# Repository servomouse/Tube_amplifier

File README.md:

Not that i am a fan of a high quality music, rather I love vacuum tubes and want to build something out of them. So, here it is: my vacuum tube headphone amplifier (but actually it can output up to 2 watts per channel). It is not finished yet, so the schematic may change during the experiments

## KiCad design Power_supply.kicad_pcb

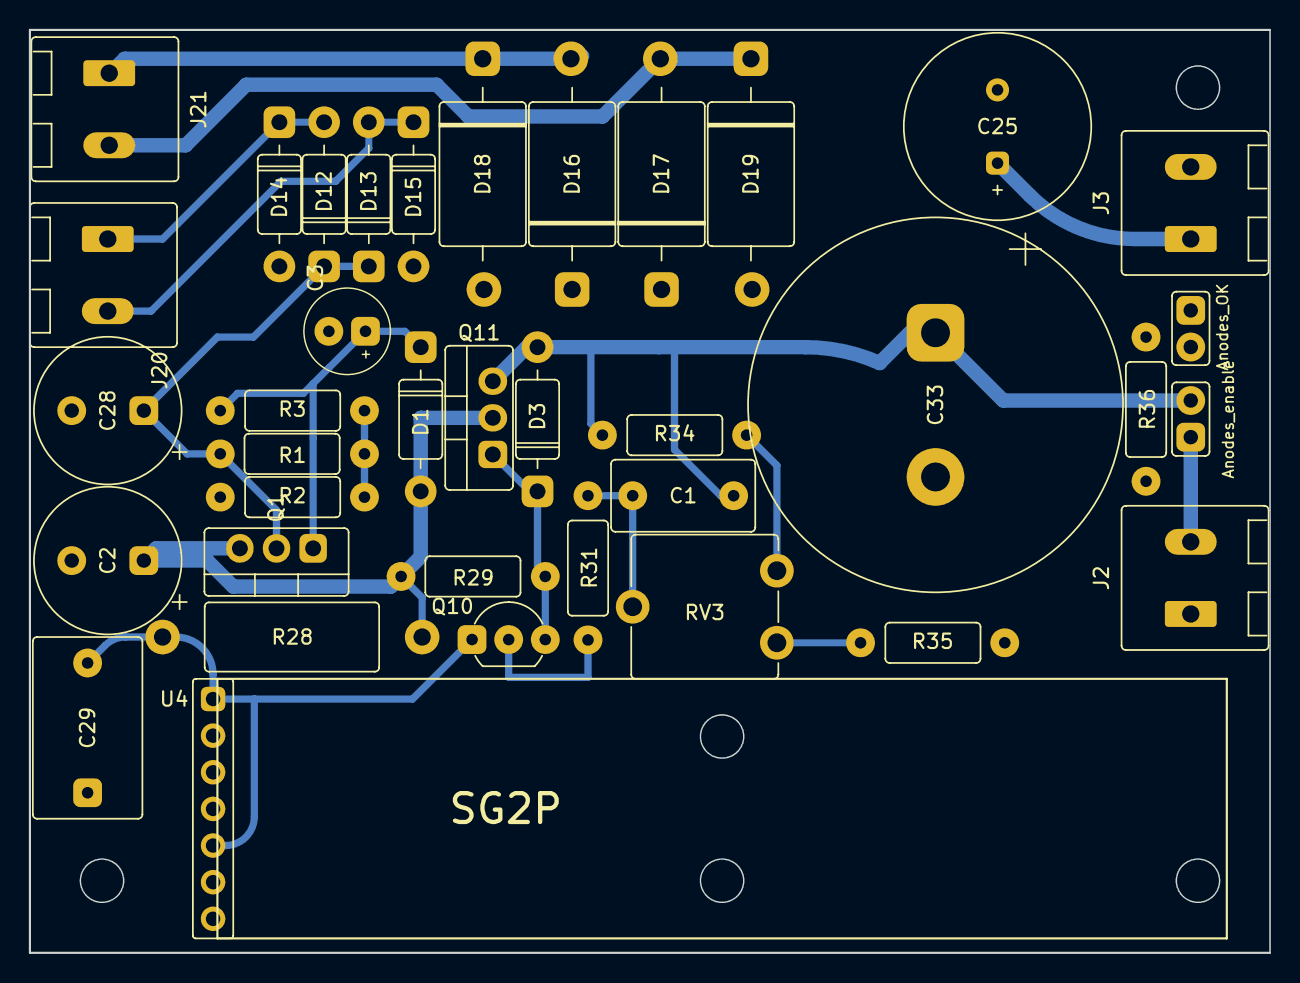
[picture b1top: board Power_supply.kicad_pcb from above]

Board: 2 copper layers, 86.0 x 64.0 mm, 37 parts (0 on the bottom side), 19 nets.

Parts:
C1: 33n; C_THT_K73-17_P7.00mm
C2, C28: 10uF; C_THT_D10.0mm_P5.00mm
C3: 2,2uF; C_THT_D5.0mm_P2.54mm
C25: 3300uF_10V; C_THT_D13mm_P5.08mm
C29: 100n; C_THT_K73-17_P9.00mm
C33: 100uF; CP_Radial_D22.0mm_P10.00mm_SnapIn
D1, D3: 1N4740A; D_DO-41_short
D12, D13, D14, D15: 1n4007; D_DO-41_short
D16, D17, D18, D19: 1N5821; D_DO-27_P16mm_Horizontal
J2: 240V; MCV_1,5_4-G-5.0_1x02_P5.0mm_Vertical
J3: 6V3; MCV_1,5_4-G-5.0_1x02_P5.0mm_Vertical
J20: HV_Transformer; MCV_1,5_4-G-5.0_1x02_P5.0mm_Vertical
J21: LV_Transformer; MCV_1,5_4-G-5.0_1x02_P5.0mm_Vertical
J25: Anodes_enable; PinHeader_1x02_P2.54mm
NE4: Anodes_OK; PinHeader_1x02_P2.54mm
Q1, Q11: STP4NK60ZFP(MJE13003); TO-220-3_Vertical
Q10: MPSA42; TO-92_Wide
R1: 330k; R_THT_025W
R2: 10M; R_THT_025W
R3: 100; R_THT_025W
R28: 13k; R_THT_1W
R29: 10k; R_THT_025W
R31: 100k; R_THT_025W
R34: 50k; R_THT_025W
R35: 40k; R_THT_025W
R36: 1M; R_THT_025W
RV3: 10k; Potentiometer_THT_CA9V
U4: SG2P; PinHeader_1x07_P2.54mm

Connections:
240V: J2.2, J25.1
+6V: C25.1, D16.1 (K), D17.1 (K), J3.1
GND: C2.2, C3.2, C25.2, C28.2, C29.1, C33.2, D14.2 (A), D15.2 (A), D18.2 (A), D19.2 (A), J2.1, J3.2, NE4.1, R2.1, R35.2, U4.2, U4.4, U4.7
HV: C28.1, D12.1 (K), D13.1 (K), Q1.2 (D), R1.2
unnamed: C1.1, R31.1, RV3.2
unnamed: C2.1, D1.2 (A), Q1.3 (S), Q11.2 (D), R28.1, R29.2
unnamed: C3.1, D1.1 (K), Q1.1 (G), R3.1
unnamed: C1.2, C33.1, D3.2 (A), J25.2, Q11.3 (S), R34.1, R36.2
unnamed: D3.1 (K), Q10.3 (C), Q11.1 (G), R29.1
unnamed: D12.2 (A), D14.1 (K), J20.1
unnamed: D13.2 (A), D15.1 (K), J20.2
unnamed: D16.2 (A), D18.1 (K), J21.1
unnamed: D17.2 (A), D19.1 (K), J21.2
unnamed: NE4.2, R36.1
unnamed: Q10.2 (B), R31.2
unnamed: C29.2, Q10.1 (E), R28.2, U4.1, U4.5
unnamed: R1.1, R2.2, R3.2
unnamed: R34.2, RV3.1
unnamed: R35.1, RV3.3

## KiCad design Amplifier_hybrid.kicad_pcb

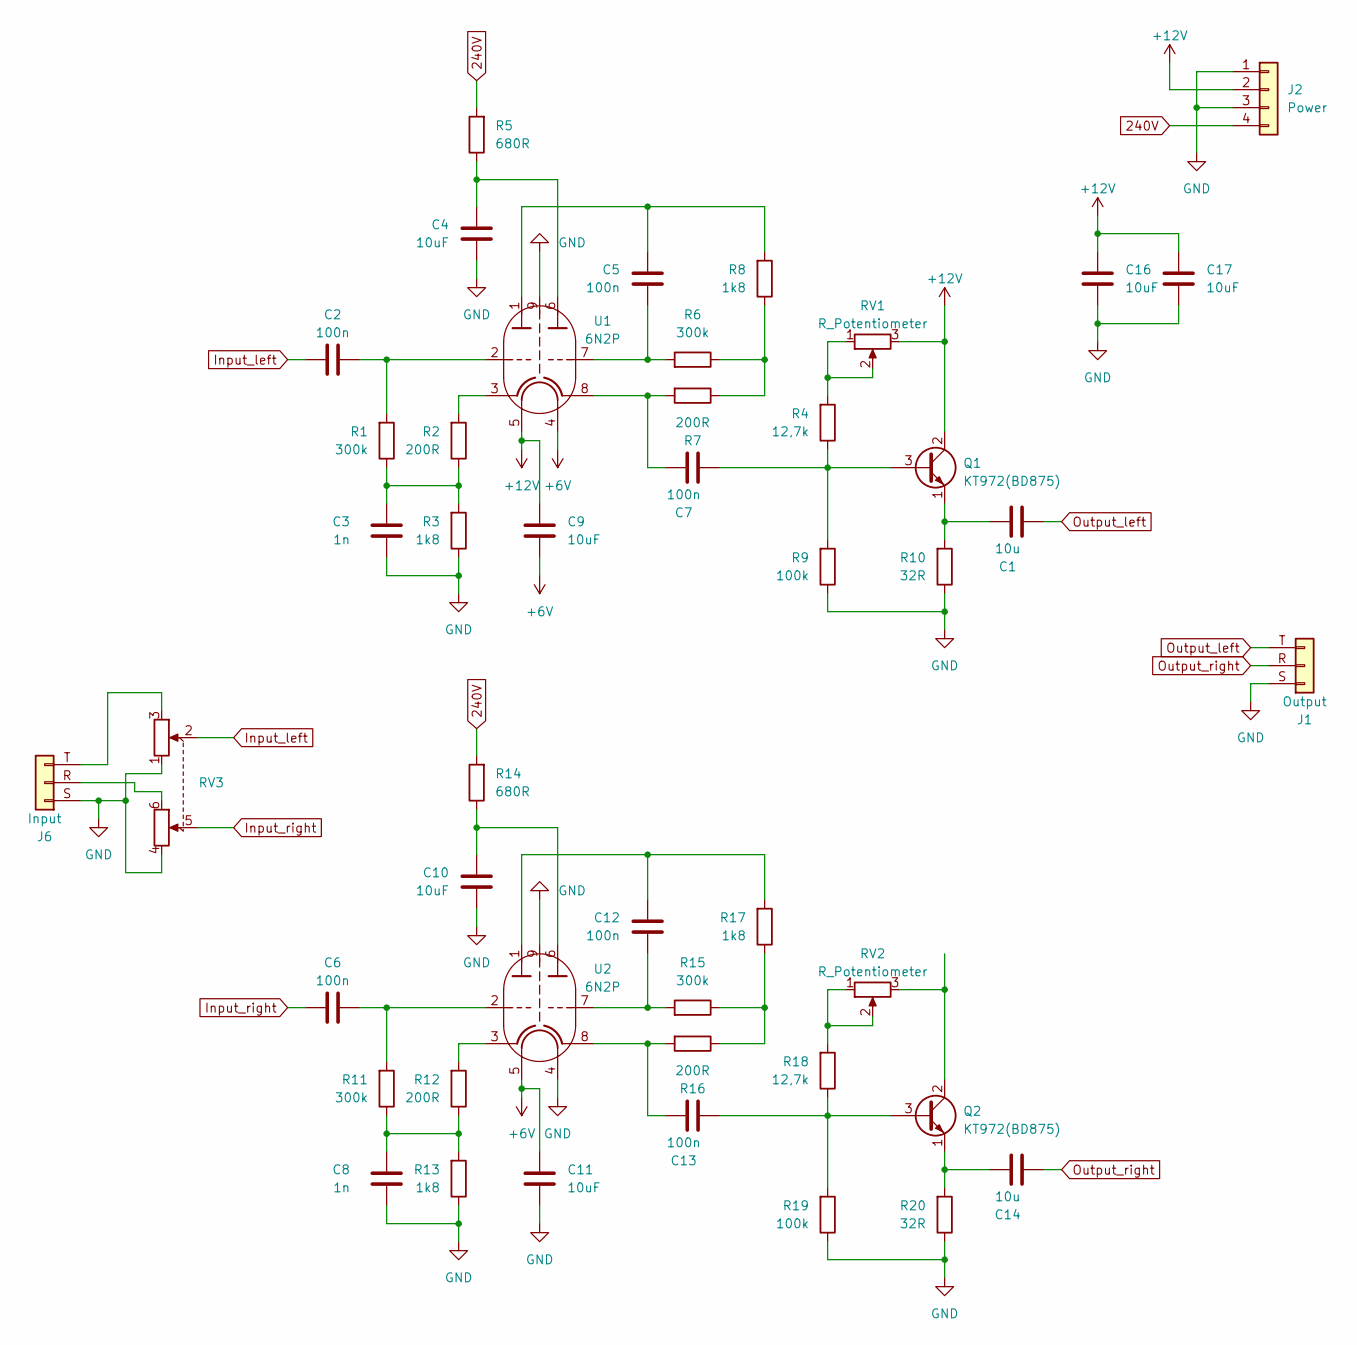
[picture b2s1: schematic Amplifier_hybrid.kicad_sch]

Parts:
C1, C14: 10u; C_THT_K73-17_P7.00mm
C2, C5, C6, C12: 100n; C_THT_K73-17_P9.00mm
C3, C8: 1n; C_THT_K73-17_P5.00mm
C4, C10, C16, C17: 10uF; C_THT_D10.0mm_P5.00mm
C7, C13: 100n; C_THT_K73-17_P7.00mm
C9, C11: 10uF; C_THT_D5.0mm_P2.54mm
J1: Output; Jack_6.35mm_Neutrik_NMJ6HFD2-AU_Horizontal
J2: Power; MCV_1,5_4-G-5.0_1x04_P5.0mm_Vertical
J6: Input; Jack_6.35mm_Neutrik_NMJ6HFD2-AU_Horizontal
Q1, Q2: КТ972(BD875); TO-126-3_Vertical
R1, R6, R11, R15: 300k; R_THT_025W
R2, R7, R12, R16: 200R; R_THT_025W
R3, R8, R13, R17: 1k8; R_THT_025W
R4, R18: 12,7k; R_THT_025W
R5, R14: 680R; R_THT_025W
R9, R19: 100k; R_THT_025W
R10, R20: 32R; R_THT_025W
RV1, RV2: R_Potentiometer; Potentiometer_THT_CA9V
RV3: R_Potentiometer_Dual; Potentiometer_Piher_T-16H_Double_Horizontal
U1, U2: 6N2P; PinHeader_1x09_P2.54mm

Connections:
240V: J2.4, R5.2, R14.2
+6V: C9.2, C11.1, U1.4, U2.5
+12V: C9.1, C16.1, C17.1, J2.2, Q1.2 (C), RV1.3, U1.5
GND: C3.2, C4.2, C8.2, C10.2, C11.2, C16.2, C17.2, J1.S (GND), J2.1, J2.3, J6.S (GND), R3.1, R9.1, R10.1, R13.1, R19.1, R20.1, RV3.1, RV3.4, U1.9, U2.4, U2.9
Input_left: C2.1, RV3.2
Input_right: C6.1, RV3.5
unnamed: C2.2, R1.2, U1.2
unnamed: C3.1, R1.1, R2.1, R3.2
unnamed: C4.1, R5.1, U1.6
unnamed: C5.1, R6.2, U1.7
unnamed: C5.2, R8.2, U1.1
unnamed: C6.2, R11.2, U2.2
unnamed: C7.1, R7.2, U1.8
unnamed: C8.1, R11.1, R12.1, R13.2
unnamed: C10.1, R14.1, U2.6
unnamed: C12.1, R15.2, U2.7
unnamed: C12.2, R17.2, U2.1
unnamed: C13.1, R16.2, U2.8
unnamed: J6.T (L), RV3.3
unnamed: J6.R, RV3.6
unnamed: C7.2, Q1.3 (B), R4.1, R9.2
unnamed: C1.1, Q1.1 (E), R10.2
unnamed: C13.2, Q2.3 (B), R18.1, R19.2
unnamed: Q2.2 (C), RV2.3
unnamed: C14.1, Q2.1 (E), R20.2
unnamed: R2.2, U1.3
unnamed: R4.2, RV1.1, RV1.2
unnamed: R6.1, R7.1, R8.1
unnamed: R12.2, U2.3
unnamed: R15.1, R16.1, R17.1
unnamed: R18.2, RV2.1, RV2.2
Output_left: C1.2, J1.T (L)
Output_right: C14.2, J1.R

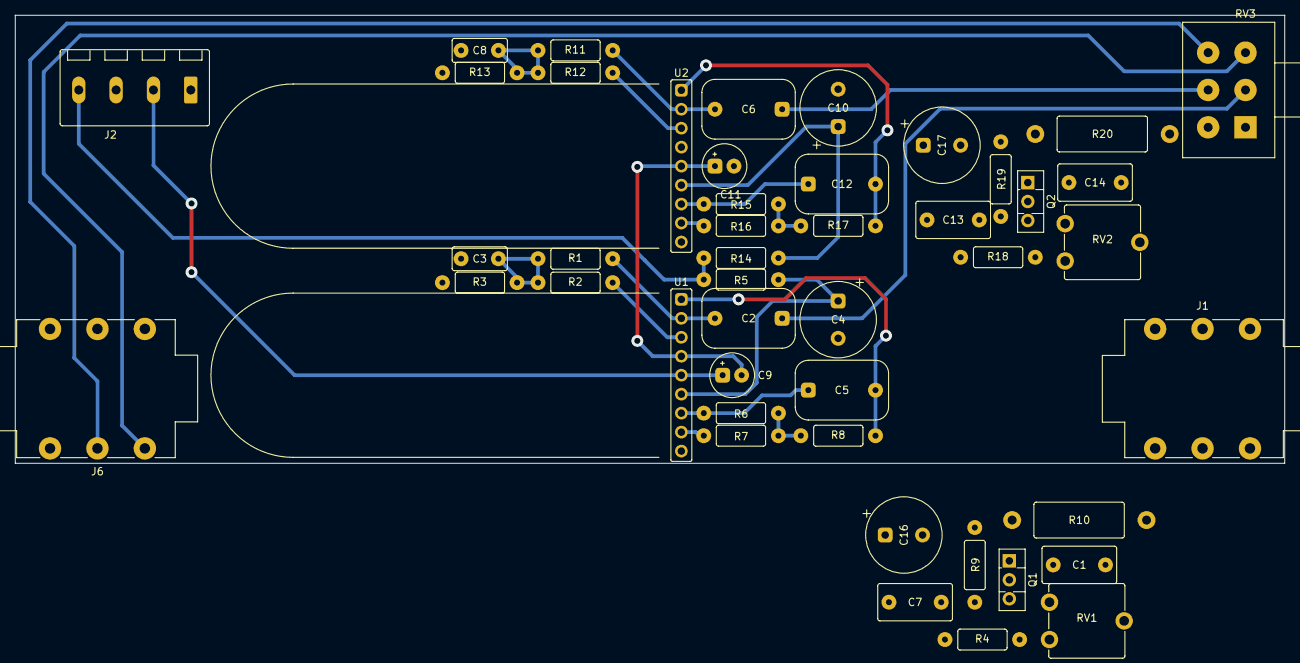
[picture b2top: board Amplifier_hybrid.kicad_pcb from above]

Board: 2 copper layers, 170.0 x 60.0 mm, 46 parts (0 on the bottom side), 33 nets.

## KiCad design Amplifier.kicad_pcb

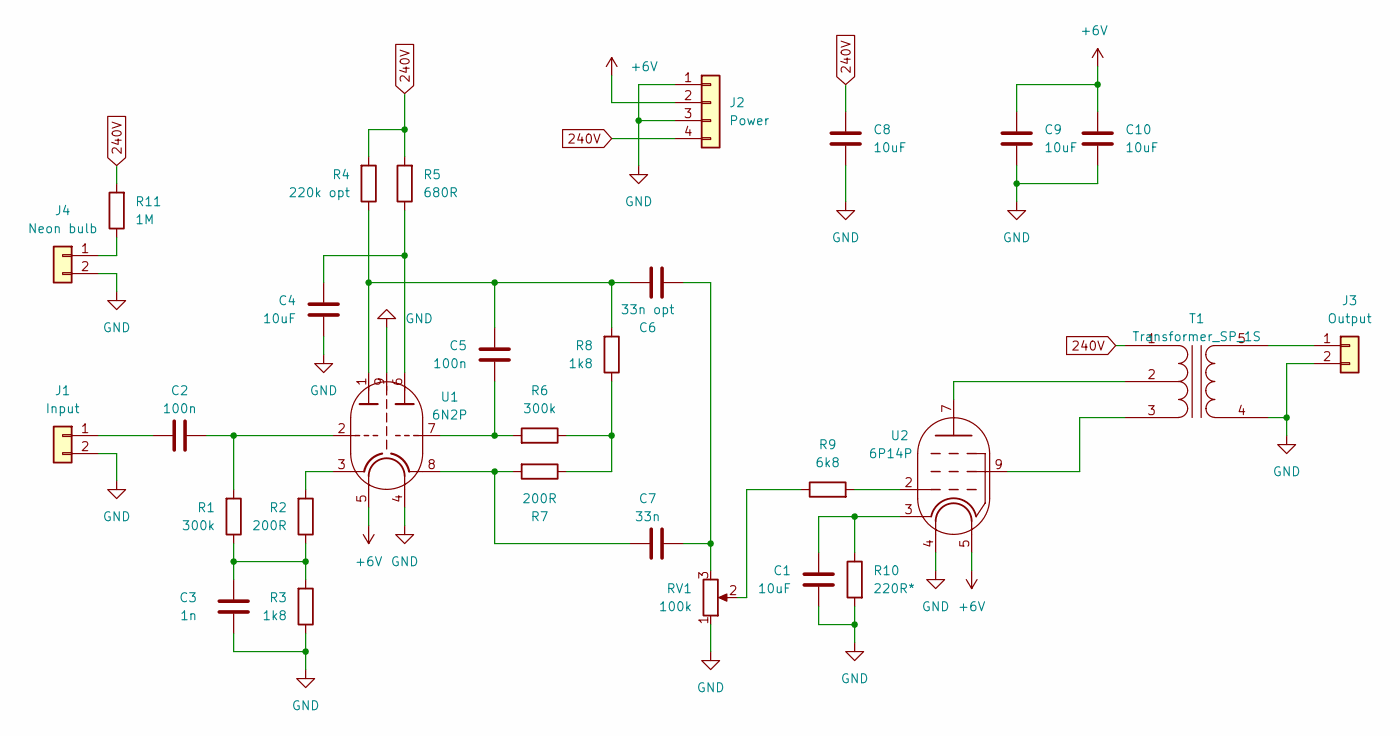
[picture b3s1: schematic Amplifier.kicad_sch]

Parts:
C1, C4, C8: 10uF; C_THT_D10.0mm_P5.00mm
C2, C5: 100n; C_THT_K73-17_P9.00mm
C3: 1n; C_THT_K73-17_P5.00mm
C6: 33n opt; C_THT_K73-17_P7.00mm
C7: 33n; C_THT_K73-17_P7.00mm
C9, C10: 10uF; C_THT_D5.0mm_P2.54mm
J1: Input; PinHeader_1x02_P2.54mm
J2: Power; MCV_1,5_4-G-3.5_1x04_P3.50mm_Vertical
J3: Output; PinHeader_1x02_P2.54mm
J4: Neon bulb; PinHeader_1x02_P2.54mm
R1, R6: 300k; R_THT_025W
R2, R7: 200R; R_THT_025W
R3, R8: 1k8; R_THT_025W
R4: 220k opt; R_THT_025W
R5: 680R; R_THT_025W
R9: 6k8; R_THT_025W
R10: 220R*; R_THT_1W
R11: 1M; R_THT_025W
RV1: 100k; Potentiometer_THT_CA9V
T1: Transformer_SP_1S; Output_transformer
U1: 6N2P; 9-pin_tube_socket
U2: 6P14P; 9-pin_tube_socket

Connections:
240V: C8.1, J2.4, R4.2, R5.2, R11.2, T1.1 (PR1)
+6V: C9.1, C10.1, J2.2, U1.5, U2.5
GND: C1.2, C3.2, C4.2, C8.2, C9.2, C10.2, J1.2, J2.1, J2.3, J3.2, J4.2, R3.1, R10.2, RV1.1, T1.4 (S1), U1.4, U1.9, U2.4
unnamed: C1.1, R10.1, U2.3
unnamed: C2.2, R1.2, U1.2
unnamed: C3.1, R1.1, R2.1, R3.2
unnamed: C4.1, R5.1, U1.6
unnamed: C5.1, R6.2, U1.7
unnamed: C5.2, C6.1, R4.1, R8.2, U1.1
unnamed: C6.2, C7.2, RV1.3
unnamed: C7.1, R7.2, U1.8
unnamed: C2.1, J1.1
unnamed: J3.1, T1.5 (S2)
unnamed: J4.1, R11.1
unnamed: R2.2, U1.3
unnamed: R6.1, R7.1, R8.1
unnamed: R9.1, RV1.2
unnamed: R9.2, U2.2
unnamed: T1.2 (PM), U2.7
unnamed: T1.3 (PR2), U2.9

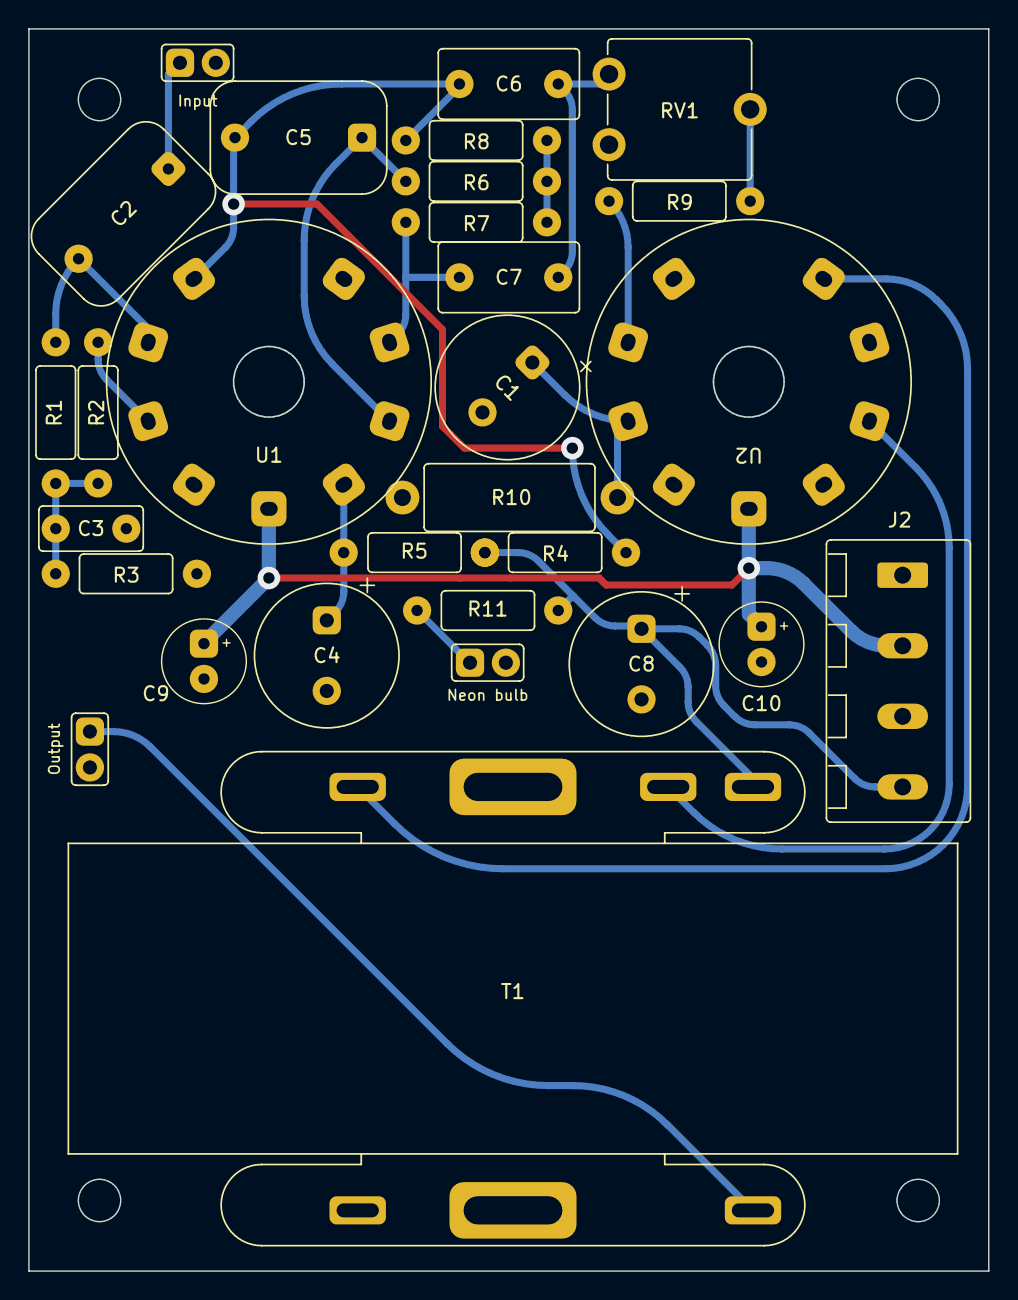
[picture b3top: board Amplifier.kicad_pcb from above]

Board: 2 copper layers, 68.0 x 88.0 mm, 29 parts (0 on the bottom side), 20 nets.

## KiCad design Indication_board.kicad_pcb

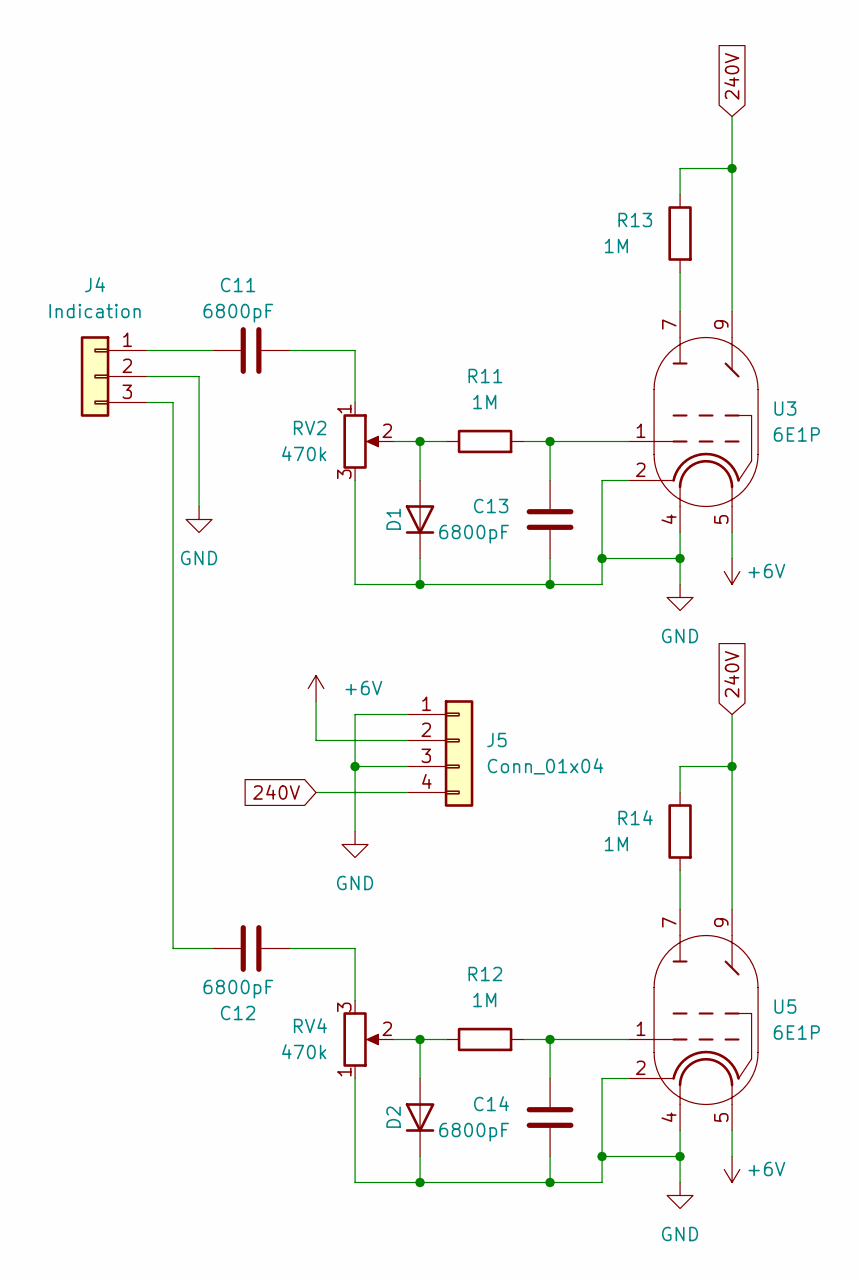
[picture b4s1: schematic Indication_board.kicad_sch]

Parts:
C11, C12, C13, C14: 6800pF; C_THT_K73-17_P5.00mm
D1, D2: 1n4007; D_DO-41_SOD81_P12.70mm_Horizontal
J4: Indication; PinHeader_1x03_P2.54mm
J5: Conn_01x04; PinHeader_1x04_P2.54mm
R11, R12, R13, R14: 1M; R_THT_025W
RV2, RV4: 470k; Potentiometer_THT_CA9V
U3, U5: 6E1P; 9-pin_tube_socket

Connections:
240V: J5.4, R13.1, R14.1, U3.9, U5.9
+6V: J5.2, U3.5, U5.5
GND: C13.2, C14.2, D1.1 (K), D2.1 (K), J4.2, J5.1, J5.3, RV2.3, RV4.1, U3.2, U3.4, U5.2, U5.4
unnamed: C11.1, J4.1
unnamed: C11.2, RV2.1
unnamed: C12.1, J4.3
unnamed: C12.2, RV4.3
unnamed: C13.1, R11.2, U3.1
unnamed: C14.1, R12.2, U5.1
unnamed: D1.2 (A), R11.1, RV2.2
unnamed: D2.2 (A), R12.1, RV4.2
unnamed: R13.2, U3.7
unnamed: R14.2, U5.7

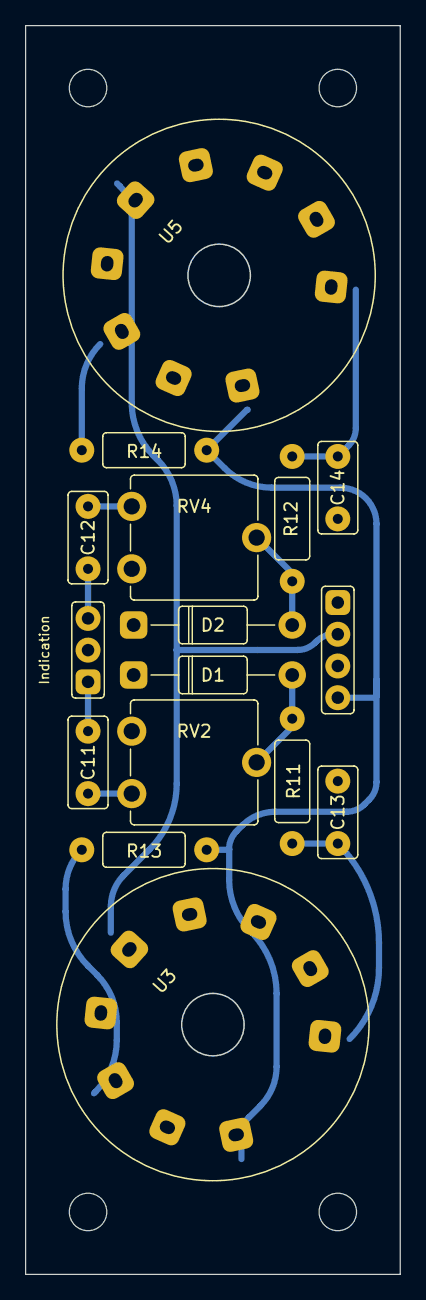
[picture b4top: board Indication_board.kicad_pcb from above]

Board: 2 copper layers, 30.0 x 100.0 mm, 16 parts (0 on the bottom side), 13 nets.

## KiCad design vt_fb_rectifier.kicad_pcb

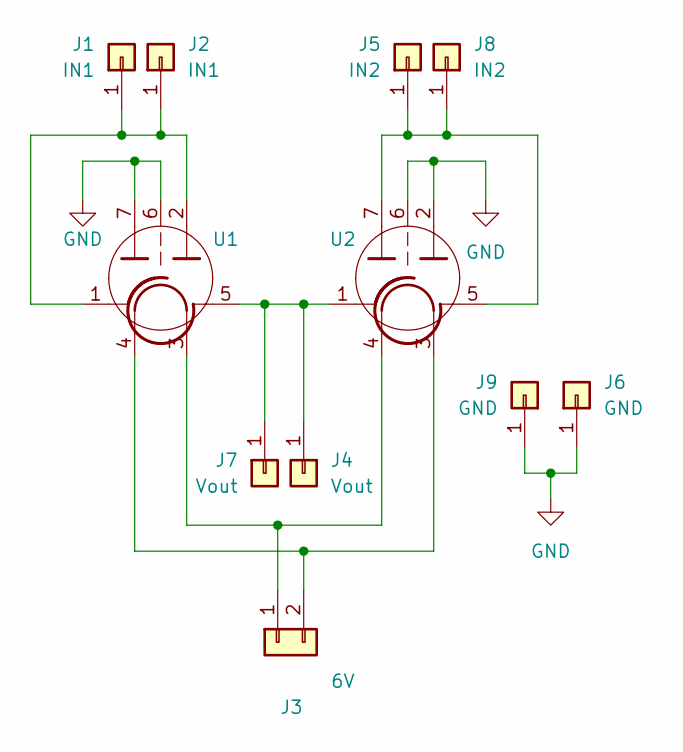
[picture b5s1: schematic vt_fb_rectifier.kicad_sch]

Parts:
J1, J2: IN1; PinHeader_1x01_P2.54mm_Vertical
J3: 6V; PinHeader_1x02_P2.54mm
J4, J7: Vout; PinHeader_1x01_P2.54mm_Vertical
J5, J8: IN2; PinHeader_1x01_P2.54mm_Vertical
J6, J9: GND; PinHeader_1x01_P2.54mm_Vertical
U1, U2: 6H2P; 7-pin_tube_socket

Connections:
GND: J6.1, J9.1, U1.6, U1.7, U2.2, U2.6
unnamed: J1.1, J2.1, U1.1, U1.2
unnamed: J3.1, U1.3, U2.4
unnamed: J3.2, U1.4, U2.3
unnamed: J4.1, J7.1, U1.5, U2.1
unnamed: J5.1, J8.1, U2.5, U2.7

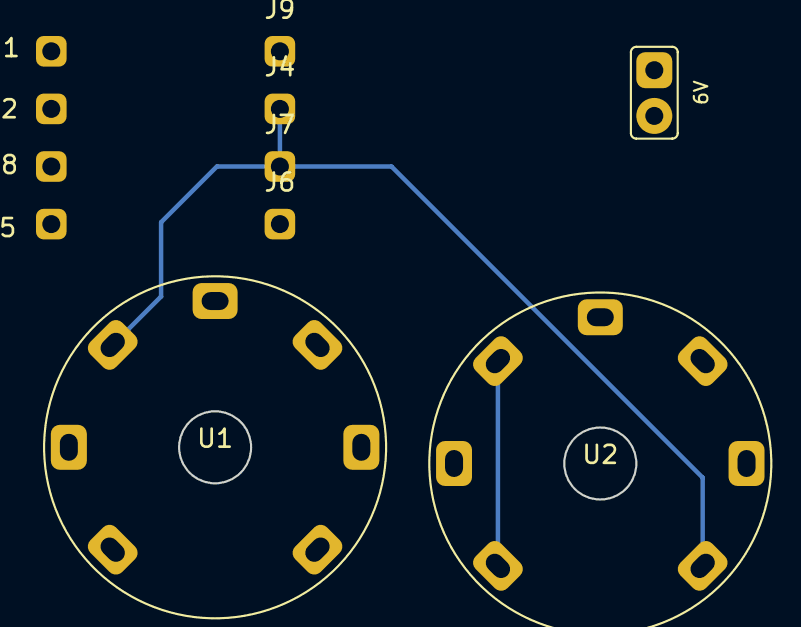
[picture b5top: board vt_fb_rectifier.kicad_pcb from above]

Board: 2 copper layers, 11 parts (0 on the bottom side), 6 nets.

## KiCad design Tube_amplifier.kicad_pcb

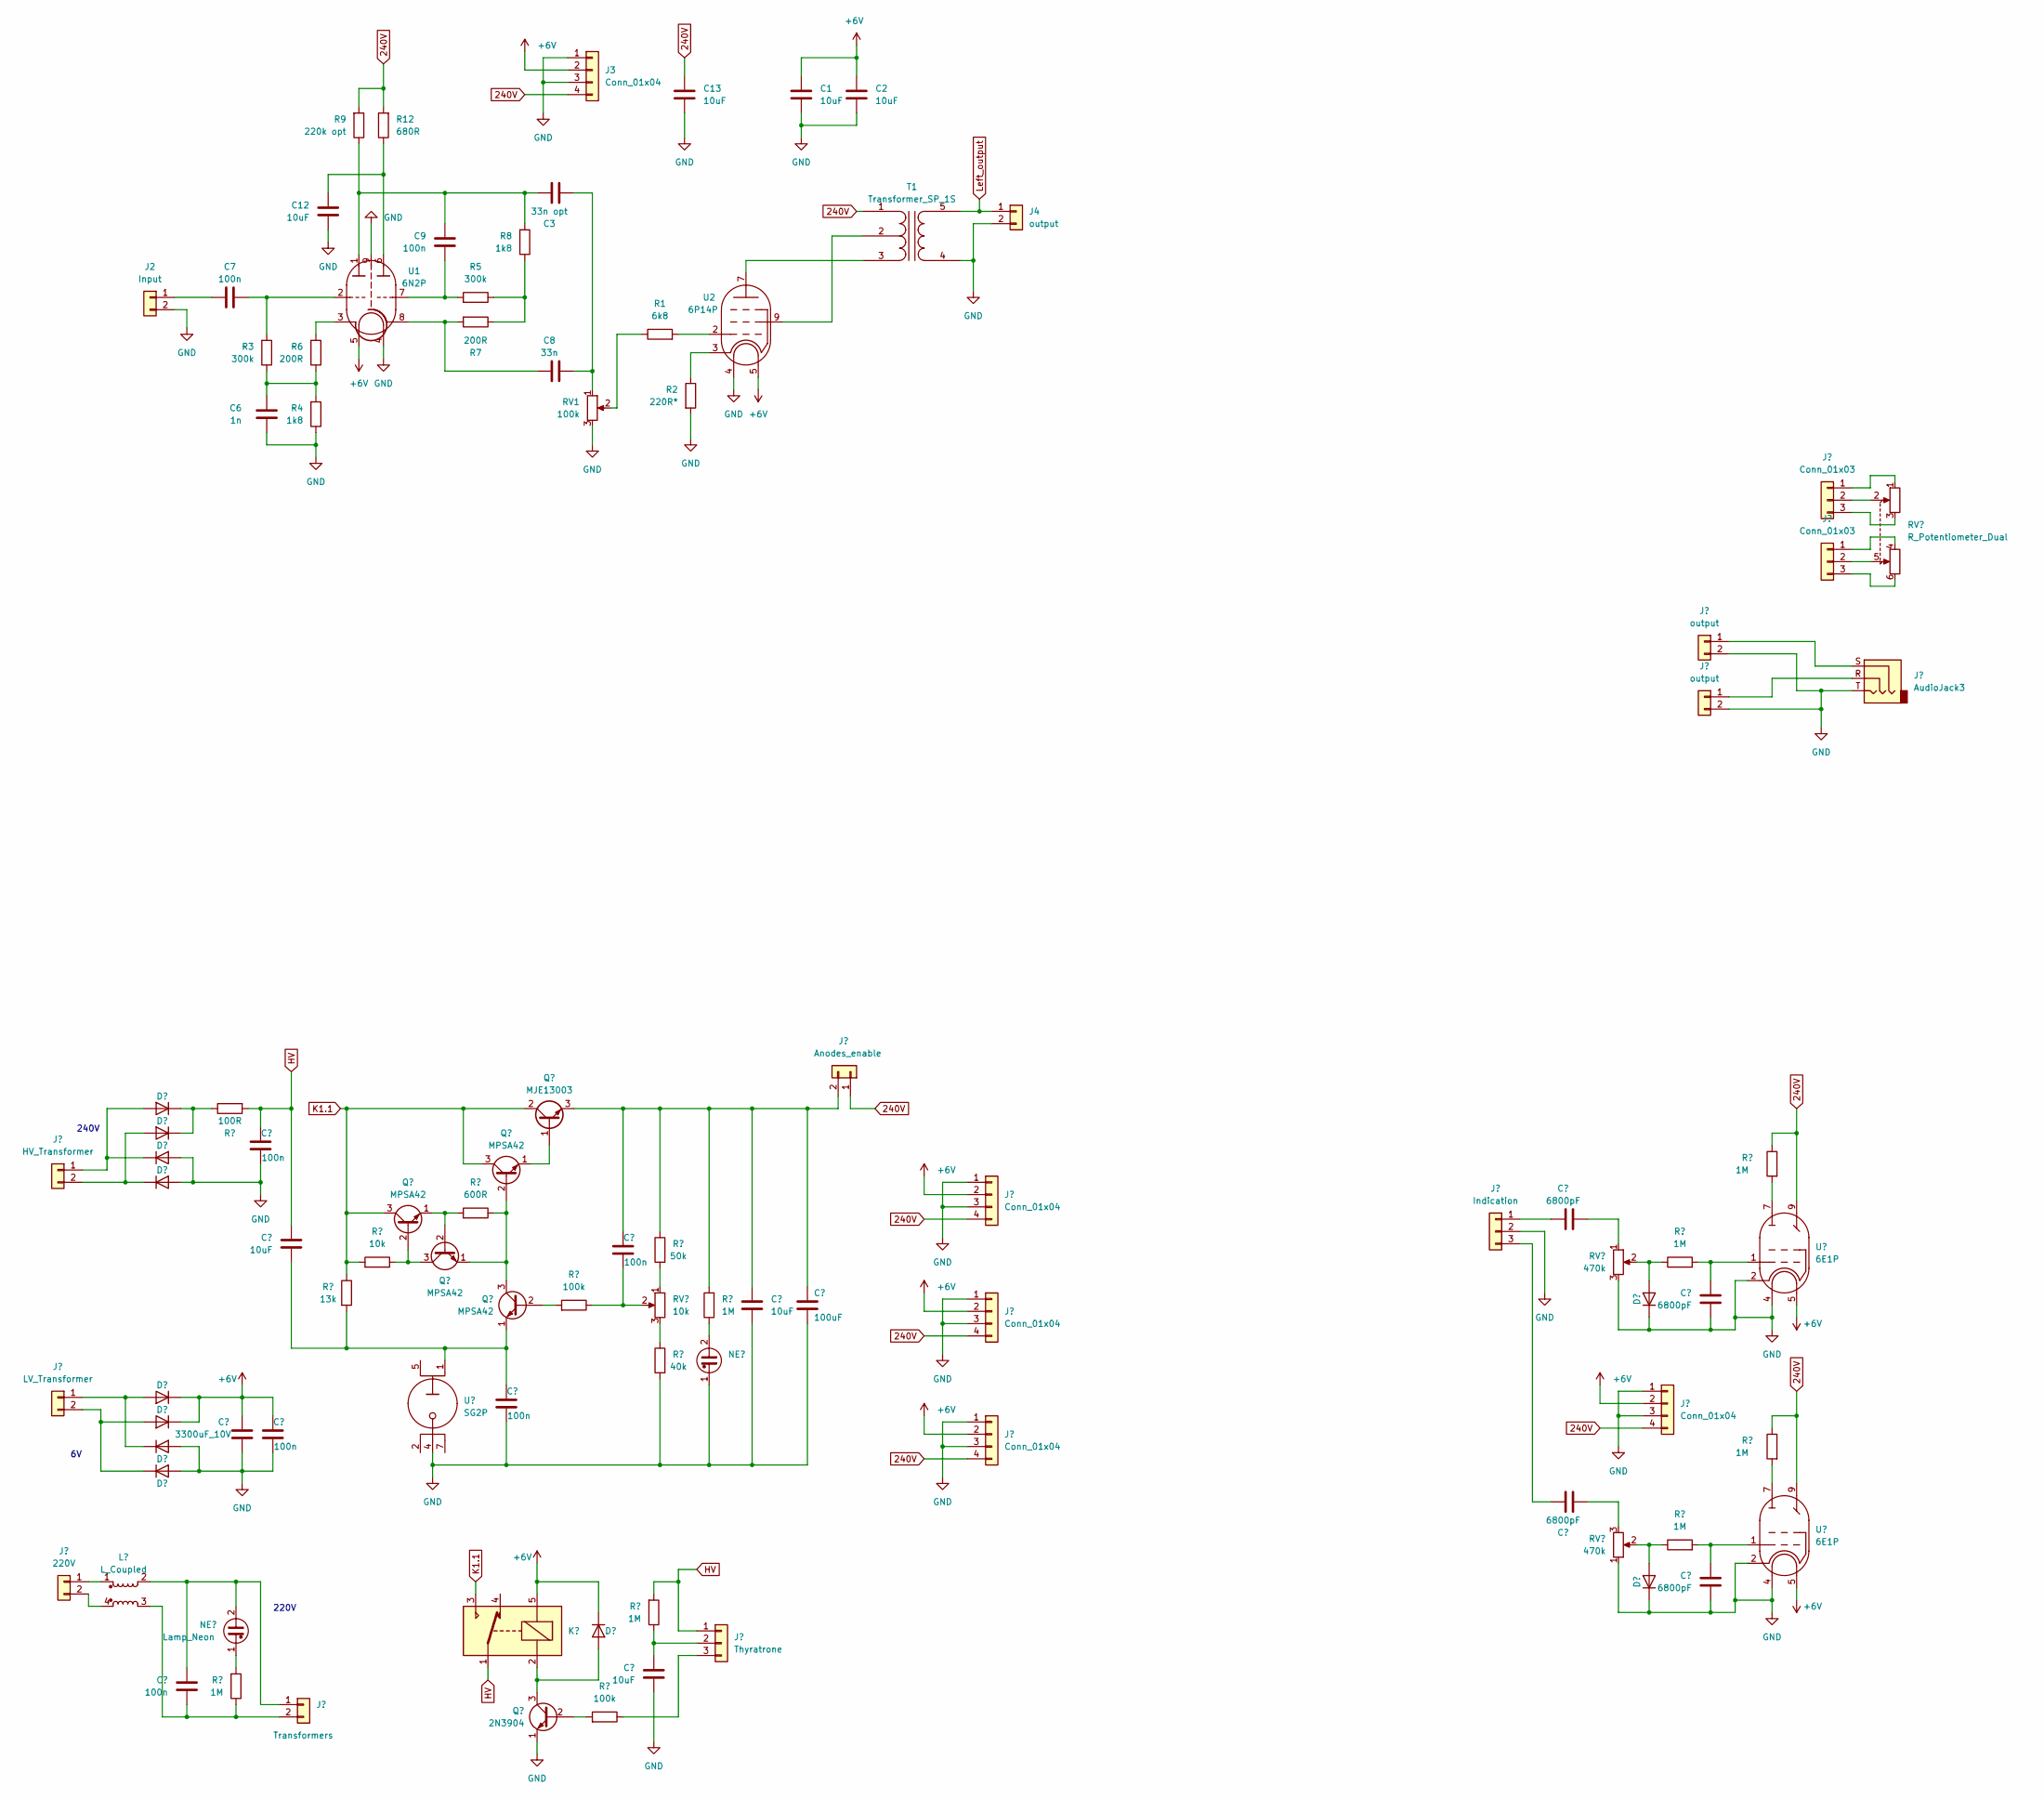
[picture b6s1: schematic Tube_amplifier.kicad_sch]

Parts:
C1, C2: 10uF; CP_Radial_D5.0mm_P2.00mm
C3: 33n opt; C_Rect_L7.2mm_W3.0mm_P5.00mm_FKS2_FKP2_MKS2_MKP2
C6: 1n; C_THT_K73-17_P5.00mm
C7, C9: 100n; C_THT_K73-17_P9.00mm
C8: 33n; C_Rect_L7.2mm_W3.0mm_P5.00mm_FKS2_FKP2_MKS2_MKP2
C12, C13: 10uF; C_THT_D10.0mm_P5.00mm
J2: Input; PinHeader_1x02_P2.54mm
J3: Conn_01x04; PinHeader_1x04_P2.54mm
J4: output; PinHeader_1x02_P2.54mm
R1: 6k8; R_THT_025W
R2: 220R*; R_THT_1W
R3, R5: 300k; R_THT_025W
R4, R8: 1k8; R_THT_025W
R6, R7: 200R; R_THT_025W
R9: 220k opt; R_THT_025W
R12: 680R; R_THT_025W
RV1: 100k; Potentiometer_THT_CA9V
T1: Transformer_SP_1S; Output_transformer
U1: 6N2P; 9-pin_tube_socket
U2: 6P14P; 9-pin_tube_socket

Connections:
240V: C13.1, J3.4, R9.2, R12.2, T1.1 (PR1)
+6V: C1.1, C2.1, J3.2, U1.5, U2.5
GND: C1.2, C2.2, C6.2, C12.2, C13.2, J2.2, J3.1, J3.3, J4.2, R2.2, R4.1, RV1.3, T1.4 (S1), U1.4, U1.9, U2.4
Left_output: J4.1, T1.5 (S2)
unnamed: C3.1, C9.2, R8.2, R9.1, U1.1
unnamed: C3.2, C8.2, RV1.1
unnamed: C6.1, R3.1, R4.2, R6.1
unnamed: C7.1, J2.1
unnamed: C7.2, R3.2, U1.2
unnamed: C8.1, R7.2, U1.8
unnamed: C9.1, R5.2, U1.7
unnamed: C12.1, R12.1, U1.6
unnamed: R1.1, RV1.2
unnamed: R1.2, U2.2
unnamed: R2.1, U2.3
unnamed: R5.1, R7.1, R8.1
unnamed: R6.2, U1.3
unnamed: T1.2 (PM), U2.9
unnamed: T1.3 (PR2), U2.7

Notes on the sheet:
240V
220V

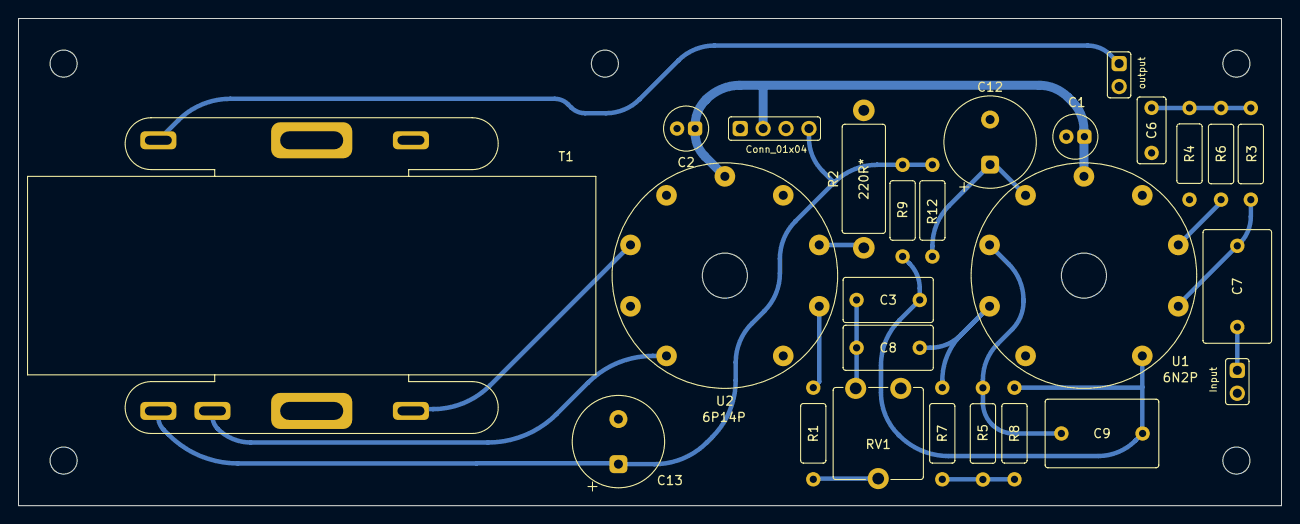
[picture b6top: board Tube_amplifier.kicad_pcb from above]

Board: 2 copper layers, 140.0 x 54.0 mm, 26 parts (0 on the bottom side), 19 nets.

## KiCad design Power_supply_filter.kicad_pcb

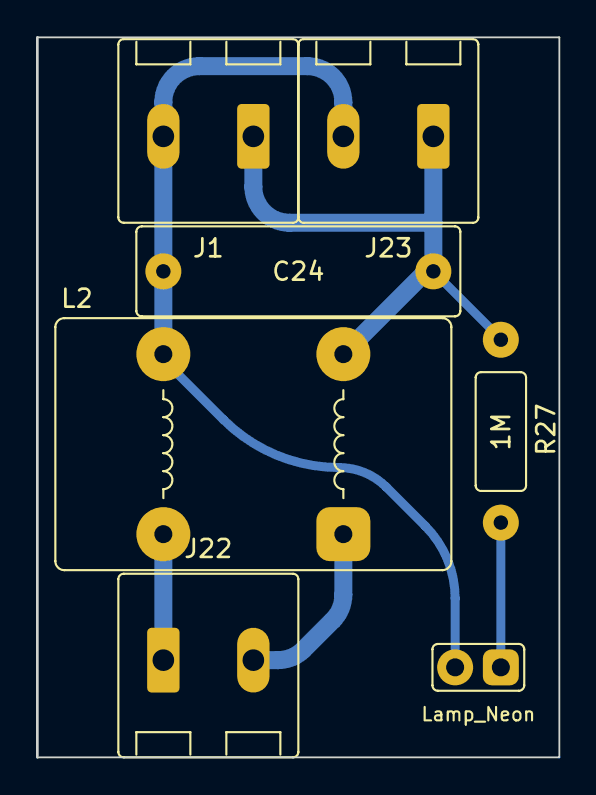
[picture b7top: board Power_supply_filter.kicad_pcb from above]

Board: 2 copper layers, 29.0 x 40.0 mm, 7 parts (0 on the bottom side), 5 nets.

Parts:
C24: 100n; C_THT_K73-17_P15.00mm
J1, J23: Transformers; MCV_1,5_4-G-5.0_1x02_P5.0mm_Vertical
J22: 220V; MCV_1,5_4-G-5.0_1x02_P5.0mm_Vertical
L2: L_Coupled; L_THT_B82731-T
NE3: Lamp_Neon; PinHeader_1x02_P2.54mm
R27: 1M; R_THT_025W

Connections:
unnamed: C24.2, J1.1, J23.1, L2.2, R27.1
unnamed: C24.1, J1.2, J23.2, L2.3, NE3.2
unnamed: J22.1, L2.4
unnamed: J22.2, L2.1
unnamed: NE3.1, R27.2

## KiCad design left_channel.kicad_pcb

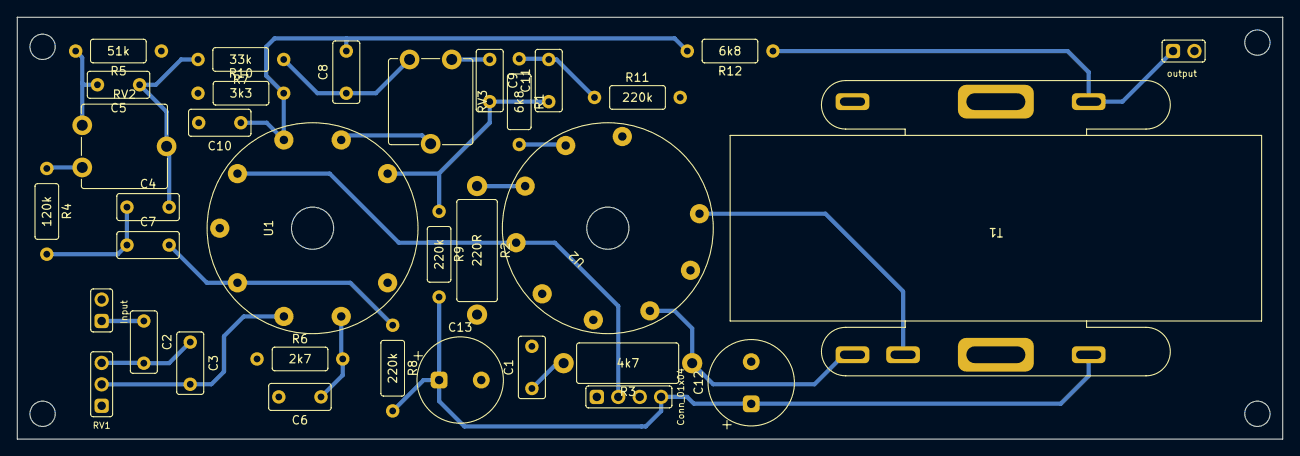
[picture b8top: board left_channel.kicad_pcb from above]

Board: 2 copper layers, 150.0 x 50.0 mm, 34 parts (0 on the bottom side), 24 nets.

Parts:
C1: 1500pF; C_THT_K73-17_P5.00mm
C2: 0,047uF; C_THT_K73-17_P5.00mm
C3: 27pF; C_THT_K73-17_P5.00mm
C4, C8, C10: 2200pF; C_THT_K73-17_P5.00mm
C5: 4700pF; C_THT_K73-17_P5.00mm
C6: 0,01uF; C_THT_K73-17_P5.00mm
C7: 0,033uF; C_THT_K73-17_P5.00mm
C9: 5,6pF; C_THT_K73-17_P5.00mm
C11: 3300pF; C_THT_K73-17_P5.00mm
C12, C13: 10uF; C_THT_D10.0mm_P5.00mm
J2: Input; PinHeader_1x02_P2.54mm
J3: Conn_01x04; PinHeader_1x04_P2.54mm
J4: output; PinHeader_1x02_P2.54mm
R1, R12: 6k8; R_THT_025W
R2: 220R; R_THT_1W
R3: 4k7; R_THT_1W
R4: 120k; R_THT_025W
R5: 51k; R_THT_025W
R6: 2k7; R_THT_025W
R7: 33k; R_THT_025W
R8, R9, R11: 220k; R_THT_025W
R10: 3k3; R_THT_025W
RV1: 470k; PinHeader_1x03_P2.54mm
RV2: 2,2M; Potentiometer_THT_CA9V
RV3: 1M; Potentiometer_THT_CA9V
T1: Transformer_SP_1S; Output_transformer
U1: 6N2P; 9-pin_tube_socket
U2: 6P14P; 9-pin_tube_socket

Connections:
240V: C12.1, C13.1, J3.4, R8.2, R9.2, T1.3 (PR2)
+6V: J3.2, U1.4, U2.4
GND: C1.2, C6.2, C10.2, C12.2, C13.2, J2.2, J3.1, J3.3, J4.2, R2.2, R5.1, R6.1, R10.1, R11.2, RV1.1, T1.5 (S2), U1.5, U1.9, U2.5
Left_output: J4.1, R12.1, T1.4 (S1)
unnamed: C1.1, R3.2
unnamed: C2.1, J2.1
unnamed: C2.2, C3.1, RV1.3
unnamed: C3.2, RV1.2, U1.7
unnamed: C4.1, C7.1, R4.2
unnamed: C4.2, C5.1, R7.2, RV2.2
unnamed: C5.2, R5.2, RV2.3
unnamed: C6.1, R6.2, U1.8
unnamed: C7.2, R8.1, U1.6
unnamed: C8.1, R7.1, RV3.1
unnamed: C9.1, RV3.3
unnamed: C8.2, C10.1, R10.2, R12.2, U1.3
unnamed: C9.2, C11.1, R9.1, U1.1
unnamed: C11.2, R1.1, R11.1
unnamed: R1.2, U2.2
unnamed: R2.1, U2.3
unnamed: R3.1, T1.1 (PR1), U2.7
unnamed: R4.1, RV2.1
unnamed: RV3.2, U1.2
unnamed: T1.2 (PM), U2.9

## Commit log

2022-12-05 Schematicks_added
2022-12-11 Some tubes added
2022-12-13 7-pin socket 3d model added
2022-12-13 Main part of schematic done
2022-12-14 Output transformer added, pcb v0.1 ready
2022-12-14 7-pin tube socket added
2022-12-16 Amplifier ready
2022-12-16 Power supply added
2022-12-17 Indication board completed
2022-12-18 Some cleaning
2023-01-04 New schematic
2023-01-04 Curved traces
2023-01-08 High Voltage stabilizer
    Create high voltage stabilizer
2023-01-08 Multiple PCB
2023-01-08 New power supply
2023-01-08 Curved traces on power supply PCB
2023-01-11 New power supply schematic
2023-01-14 Wider pads
2023-01-23 Wider pads
    First PCB version
2023-01-23 Some 3d models
2023-01-23 New power supply PCB
2023-01-24 Working on power supply PCB
2023-01-25 New power supply PCB!
2023-01-26 Power supply PCB final 1.0
2023-01-28 readme
2023-01-29 Some errors in the power supply PCB fixed
2023-01-30 Added heatsink on power mosfet
2023-02-04 New amplifier PCB
2023-02-05 Back plate 3d model
2023-02-06 Power transformer 3d model
2023-02-14 Indication board PCB
2023-02-15 New 9-pin sockets
2023-02-18 Some improvements
2023-02-19 Working with 3d models
2023-02-21 Neon bulb added on the amplifier PCB
2023-03-04 Started redesigning power supply
2023-03-05 Continue rebuilding power supply PCB
2023-03-05 PCB almost done
2023-03-07 Rounded traces
2023-03-07 Teardrops
2023-03-08 Temp
2023-03-08 New amplifier PCB with external transformer
2023-03-09 New Amplifier PCB almost ready
2023-03-10 Power supply PCB updated
2023-03-11 Rounded corners for power supply PCB
2023-03-13 More rounded corners!
2023-05-01 Hybrid Amplifier
